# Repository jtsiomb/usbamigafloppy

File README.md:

USB floppy controller for Amiga disks
=====================================

This is a USB floppy disk controller, for reading and writing amiga disks. In
conjunction with the accompanying `amigafloppy` program, it allows archiving
amiga disks as ADF disk images, or writing ADF disk images back to disks, to use
with an Amiga computer.

The firmware for this controller is based on the ArduinoFloppyDiskReader
project by Rob Smith (https://github.com/RobSmithDev/ArduinoFloppyDiskReader),
converted to run on standalone AVR hardware (as opposed to an arduino) by John
Tsiombikas.

The new AVR hardware is designed to be compatible with the original host
software, so you may use the `AmigaFloppyReader` or `AmigaFloppyReaderWin`
programs from Rob's project, if you prefer.

Directory structure:

  * `hw` - hardware: kicad files and pdf schematics.
  * `fw` - firmware for the AVR microcontroller.
  * `amigafloppy` - host program for reading/writing ADF images.

Note: The `amigafloppy` host program is not completed yet. And it's not a high
priority, since Rob's original .NET programs seem to work fine with wine on
GNU/Linux. I'd like to complete it at some stage, but I can't say when that will
happen. Contributions are of course welcome, but please coordinate with me
first. Until then, please use `AmigaFloppyReader` or `AmigaFloppyReaderWin`.

Hardware License
----------------
Copyright (C) 2018 John Tsiombikas <nuclear@member.fsf.org>

The hardware of this project is released as free/open hardware under the
Creative Commons Attribution Share-Alike license. See `LICENSE.hw` for details.

Firmware License
----------------
Copyright (C) 2017 Rob Smith <rob@robsmithdev.co.uk>

Copyright (C) 2018 John Tsiombikas <nuclear@member.fsf.org>

The microcontroller firmware of this project is released as free software,
under the terms of the GNU General Public License v3, or later.  See
`LICENSE.sw` for details.

Software License
----------------
Copyright (C) 2018 John Tsiombikas <nuclear@member.fsf.org>

The host software (amigafloppy tool) is released as free software, under the
terms of the GNU General Public License v3, or later. See `LICENSE.sw` for
details.

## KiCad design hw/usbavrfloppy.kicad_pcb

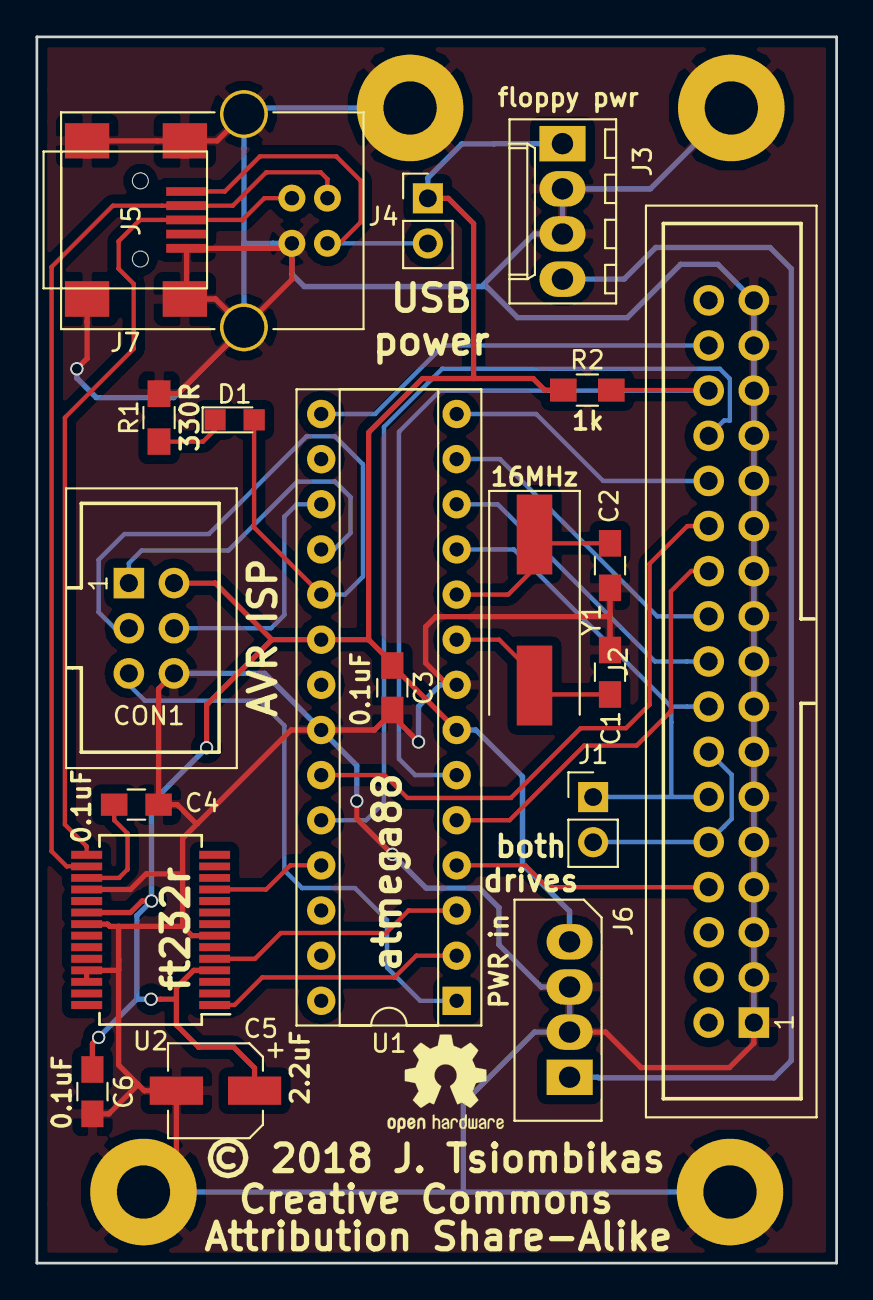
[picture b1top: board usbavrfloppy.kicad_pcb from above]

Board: 2 copper layers, 45.0 x 69.0 mm, 20 parts (0 on the bottom side), 28 nets.

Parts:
C1, C2: 22pF; C_0805_HandSoldering
C3, C4, C6: 0.1uF; C_0805_HandSoldering
C5: 2.2uF; CP_Elec_5x5.7
CON1: avr_isp; IDC_Header_Straight_6pins
D1: ACT; LED_0805
J1: bothdrv; Pin_Header_Straight_1x02_Pitch2.54mm
J2: floppy_conn; IDC_Header_Straight_34pins
J3: floppy_power; Molex_KK-6410-04_04x2.54mm_Straight
J4: usbpower; Pin_Header_Straight_1x02_Pitch2.54mm
J5: USB_B
J6: PWRIN; Molex_SPOX-5267_22-03-5045_04x2.54mm_Straight
J7: USB_OTG; USB_Mini-B
R1: 330; R_0805_HandSoldering
R2: 1k; R_0805_HandSoldering
U1: ATMEGA88A-PU; DIP-28_W7.62mm_Socket
U2: FT232RL; SSOP-28_5.3x10.2mm_Pitch0.65mm
Y1: 16MHz; Crystal_SMD_HC49-SD

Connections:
+12V: J3.4, J6.1
/CTS: U1.25, U2.11
/MISO: CON1.1, U1.18
/MOSI: CON1.4, U1.17
/RXD: U1.2, U2.1
/SCK: CON1.3, D1.2, U1.19
/TXD: U1.3, U2.5
/USBD+: J5.3, J7.3, U2.15
/USBD-: J5.2, J7.2, U2.16
/~DIR: J2.18, U1.12
/~HSEL: J2.32, U1.15
/~INDEX: J2.8, U1.4
/~MOTEN: J1.1, J2.12, J2.16, U1.11
/~RDATA: J2.30, R2.2, U1.6
/~RESET: CON1.5, U1.1
/~STEP: J2.20, U1.13
/~TRK0: J2.26, U1.14
/~WDATA: J2.22, U1.5
/~WGATE: J2.24, U1.23
/~WPROTECT: J2.28, U1.24
GND: C1.1, C2.1, C3.2, C4.1, C5.2, C6.2, CON1.6, J2.1, J2.3, J2.5, J2.7, J2.9, J2.11, J2.13, J2.15, J2.17, J2.19, J2.21, J2.23, J2.25, J2.27, J2.29, J2.31, J2.33, J3.2, J3.3, J5.4, J5.5, J6.2, J6.3, J7.5, J7.6, R1.2, U1.8, U1.22, U2.7, U2.18, U2.21, U2.25, U2.26
unnamed: C1.2, U1.9, Y1.2
unnamed: C2.2, U1.10, Y1.1
unnamed: C4.2, U2.17
unnamed: D1.1, R1.1
unnamed: J1.2, J2.10, J2.14
unnamed: J4.2, J5.1, J7.1
VCC: C3.1, C5.1, C6.1, CON1.2, J3.1, J4.1, J6.4, R2.1, U1.7, U1.20, U2.4, U2.20

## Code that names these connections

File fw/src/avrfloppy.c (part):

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#include <avr/interrupt.h>


#define INDEX_PORT			PIND
#define INDEX_BIT			0x04

#define WDATA_PORT			PORTD
#define WDATA_BIT			0x08

#define RDATA_PORT			PIND
#define RDATA_BIT			0x10

#define MOTOR_PORT			PORTD
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#define HEADSEL_PORT		PORTB
#define HEAD_SELECT_BIT		0x02

#define WGATE_PORT			PORTC
#define WGATE_BIT			0x01

#define WPROT_PORT			PINC
#define WPROT_BIT			0x02

#define CTS_PORT			PORTC
#define CTS_BIT				0x04

#define LED_PORT			PORTB
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	/* Enable writing */
	WGATE_PORT &= ~WGATE_BIT;

	/* While the INDEX pin is high wait.  Might as well write from the start of the track */
	if(wait_for_index) {
		while(INDEX_PORT & INDEX_BIT);
	}
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	/* Signal we're active */
	LED_PORT |= LED_BIT;

	/* While the INDEX pin is high wait if the other end requires us to */
	if(read_byte_from_uart()) {
		while(INDEX_PORT & INDEX_BIT);
	}
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
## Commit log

2018-03-03 added .gitignore and renamed LICENSE.fw to LICENSE.sw
2018-03-04 starting work on the amigafloppy program
2018-03-04 fixed readme markdown
2018-03-04 fixed readme formatting
2018-03-04 writing amigafloppy
2018-03-08 almost reading tracks
2018-03-08 changed the copyright statements in the readme file to reflect the decision to not include any of the original AmigaReader code, and re-write the host-side driver program from scratch.
2018-03-09 MFM decoding works, finding all sectors
2018-03-11 Reading and saving to ADF pretty much done. Only checksums and retries left to do.
2018-03-11 added copyright headers
2018-03-13 checksums and debugging
2018-03-14 ported Rob Smith's v1.2 firmware changes to the AVR firmware
2018-03-27 backported Rob's changes from firmware 1.3, which fixes the write checksum errors
2018-12-20 added a note in the readme file, about the incomplete state of the host program. To avoid further confusion of people trying to use it.

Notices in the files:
fw/src/avrfloppy.c:
Copyright (C) 2017-2018 Robert Smith (@RobSmithDev)
hw/usbavrfloppy.kicad_pcb:
© 2018 J. Tsiombikas
